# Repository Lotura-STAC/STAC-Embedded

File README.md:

# STAC-Embedded
Hardware PCB & Image

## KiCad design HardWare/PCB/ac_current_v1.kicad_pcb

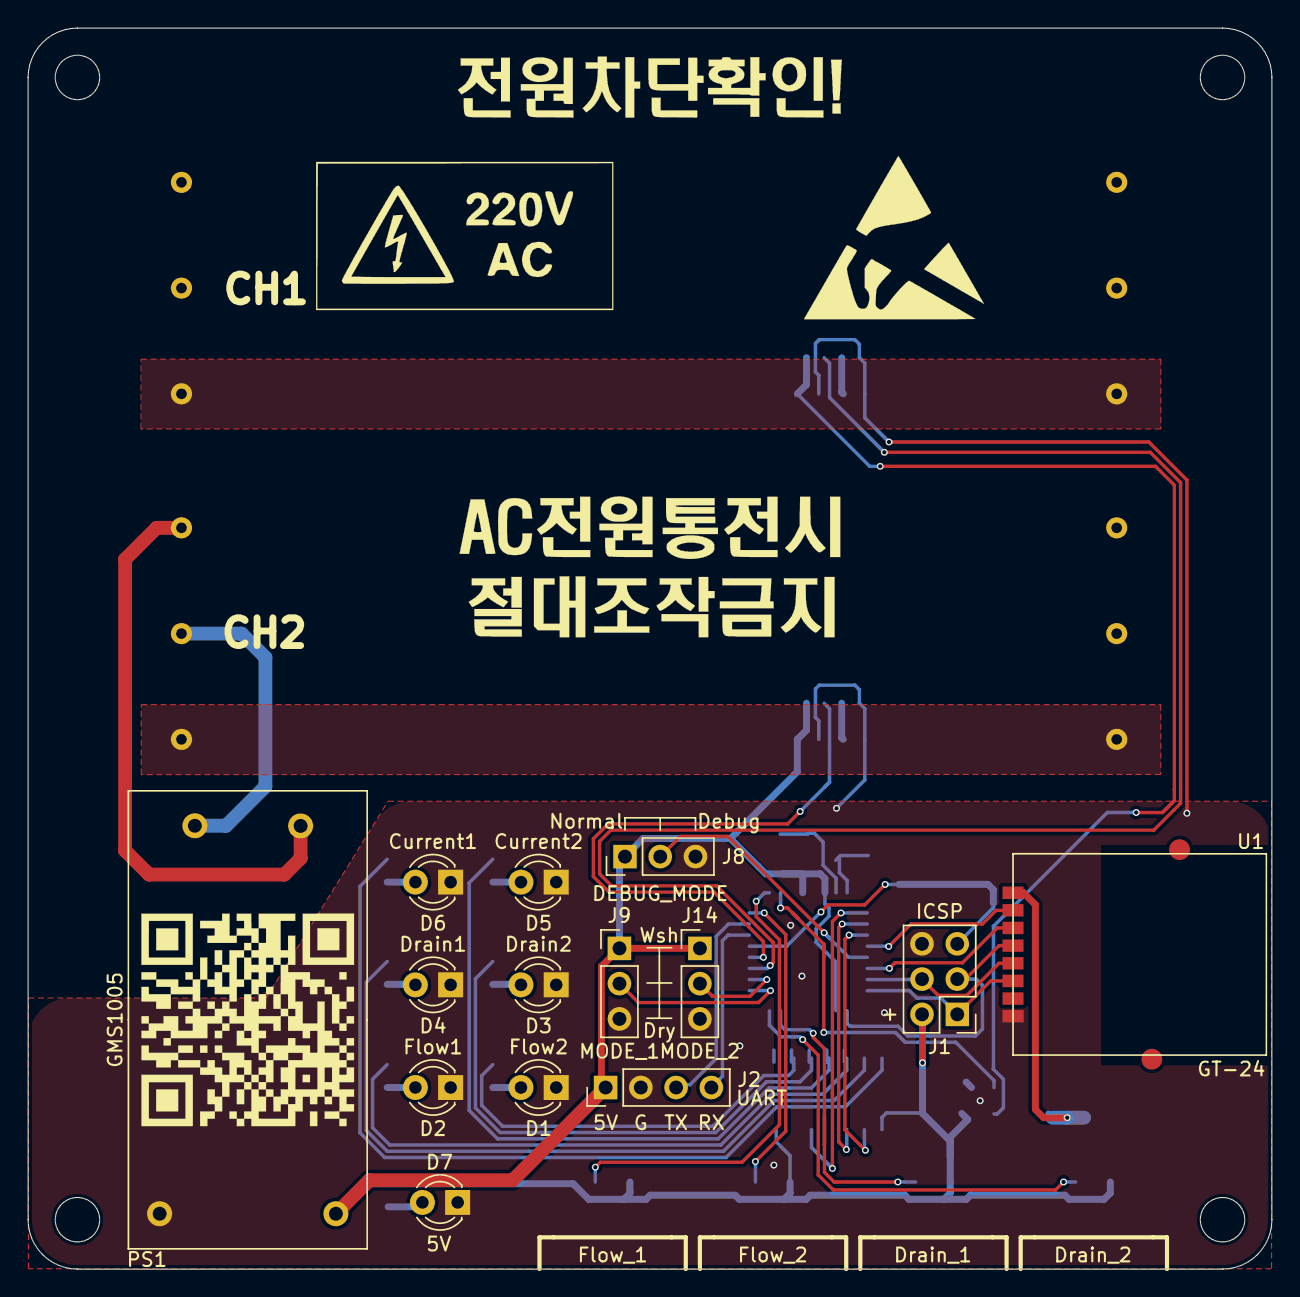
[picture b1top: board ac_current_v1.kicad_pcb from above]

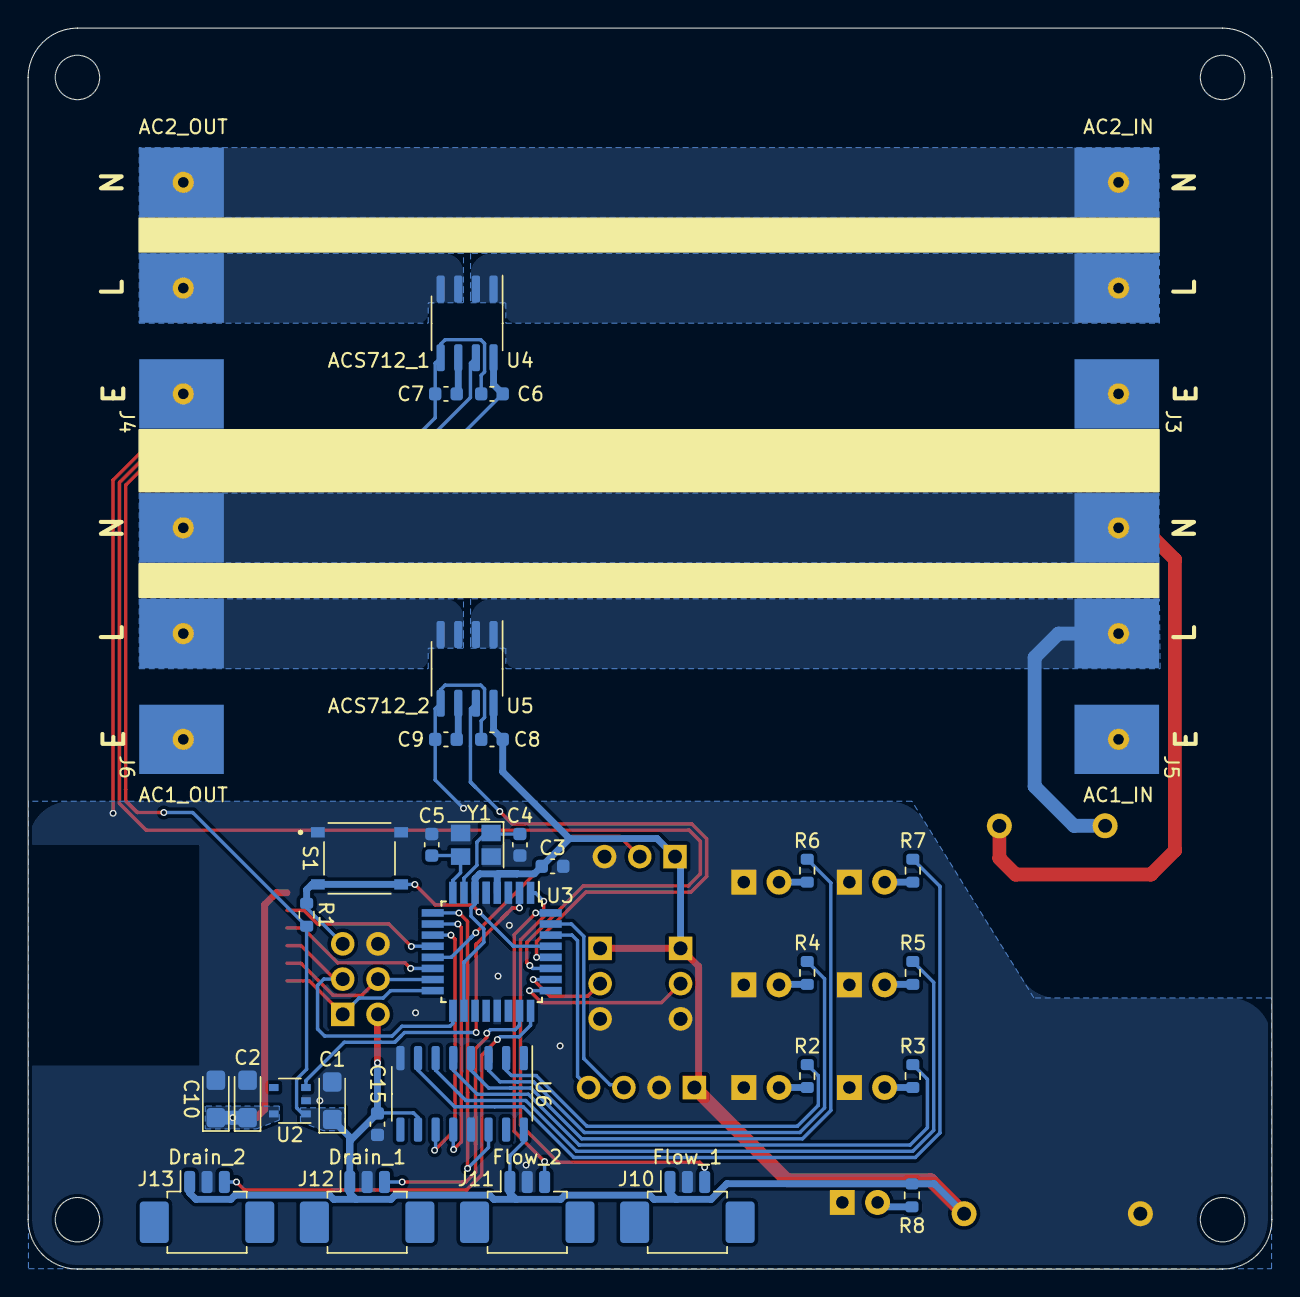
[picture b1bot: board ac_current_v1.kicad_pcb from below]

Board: 2 copper layers, 89.6 x 89.4 mm, 52 parts (34 on the bottom side), 49 nets.

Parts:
C1, C2, C10: 10uf; CP_EIA-3216-18_Kemet-A
C3, C6, C8, C15: 100nf; C_0603_1608Metric
C4, C5: 22pf; C_0603_1608Metric
C7, C9: 1nf; C_0603_1608Metric
D1: Flow2; LED_D3.0mm
D2: Flow1; LED_D3.0mm
D3: Drain2; LED_D3.0mm
D4: Drain1; LED_D3.0mm
D5: Current2; LED_D3.0mm
D6: Current1; LED_D3.0mm
D7: 5V; LED_D3.0mm
H1, H2, H3, H4: MountingHole_Pad; MountingHole_3.2mm_M3
J1: ICSP; PinHeader_2x03_P2.54mm_Vertical
J2: UART; PinHeader_1x04_P2.54mm_Vertical
J3: AC2_IN; SMD_762
J4: AC2_OUT; SMD_762
J5: AC1_IN; SMD_762
J6: AC1_OUT; SMD_762
J8: DEBUG_MODE; PinHeader_1x03_P2.54mm_Vertical
J9: MODE_1; PinHeader_1x03_P2.54mm_Vertical
J10: Flow_1; Molex_PicoBlade_53261-0371_1x03-1MP_P1.25mm_Horizontal
J11: Flow_2; Molex_PicoBlade_53261-0371_1x03-1MP_P1.25mm_Horizontal
J12: Drain_1; Molex_PicoBlade_53261-0371_1x03-1MP_P1.25mm_Horizontal
J13: Drain_2; Molex_PicoBlade_53261-0371_1x03-1MP_P1.25mm_Horizontal
J14: MODE_2; PinHeader_1x03_P2.54mm_Vertical
PS1: GMS1005; GMS0505
R1: 10k; R_0603_1608Metric
R2, R3, R4, R5, R6, R7, R8: 330; R_0603_1608Metric
S1: RST; SW_TS-1187A-B-A-B
U1: GT-24; nrf24l01 smd
U2: NCP603SN330; TSOP-5_1.65x3.05mm_P0.95mm
U3: ATmega328P-AU; TQFP-32_7x7mm_P0.8mm
U4: ACS712_1; SOIC-8_3.9x4.9mm_P1.27mm
U5: ACS712_2; SOIC-8_3.9x4.9mm_P1.27mm
U6: 74HC595; SO-16_3.9x9.9mm_P1.27mm
Y1: 16Mhz; Crystal_SMD_3225-4Pin_3.2x2.5mm

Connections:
+3V3: C2.1, C10.1, U1.1, U2.5
+5V: C1.1, C3.2, C6.1, C8.1, C15.1, J1.2, J2.1, J8.1, J9.1, J10.1, J11.1, J12.1, J13.1, J14.1, PS1.4, R1.2, R8.1, U2.1, U3.4, U3.6, U3.18, U4.8, U5.8, U6.10, U6.16
/A0: J12.3, U3.23
/A1: J13.3, U3.24
/A2: J9.2, U3.25
/A3: J14.2, U3.26
/A4: U3.27, U4.7
/A5: U3.28, U5.7
/D2: J11.3, U3.32
/D3: J10.3, U3.1
/D4: U2.3, U3.2
/D5: U3.9, U6.14
/D6: U3.10, U6.12
/D7: U3.11, U6.11
/D8: U1.2, U3.12
/D9: J8.2, U3.13
/D10: U1.3, U3.14
/D11: J1.4, U1.5, U3.15
/D12: J1.1, U1.6, U3.16
/D13: J1.3, U1.4, U3.17
/RST: J1.5, R1.1, S1.C, S1.D, U3.29
/RX: J2.4, U3.30
/TX: J2.3, U3.31
GND: C1.2, C2.2, C3.1, C4.1, C5.1, C6.2, C7.2, C8.2, C9.2, C10.2, C15.2, D1.1, D2.1, D3.1, D4.1, D5.1, D6.1, D7.1, J1.6, J2.2, J8.3, J9.3, J10.2, J11.2, J12.2, J13.2, J14.3, PS1.3, S1.A, S1.B, U1.8, U2.2, U3.3, U3.5, U3.21, U4.5, U5.5, U6.8, U6.13, Y1.2, Y1.4
GND1: J3.1, J4.1
GND2: J5.1, J6.1
LINE: J5.3, J6.3, PS1.1
NEUT: J5.2, PS1.2, U5.1, U5.2
unnamed: C4.2, U3.7, Y1.1
unnamed: C5.2, U3.8, Y1.3
unnamed: C7.1, U4.6
unnamed: C9.1, U5.6
unnamed: D1.2, R2.2
unnamed: D2.2, R3.2
unnamed: D3.2, R4.2
unnamed: D4.2, R5.2
unnamed: D5.2, R6.2
unnamed: D6.2, R7.2
unnamed: D7.2, R8.2
unnamed: J3.2, U4.1, U4.2
unnamed: J3.3, J4.3
unnamed: J4.2, U4.3, U4.4
unnamed: J6.2, U5.3, U5.4
unnamed: R2.1, U6.2
unnamed: R3.1, U6.5
unnamed: R4.1, U6.3
unnamed: R5.1, U6.6
unnamed: R6.1, U6.4
unnamed: R7.1, U6.7

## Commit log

2023-09-14 노드 펌웨어 작성, 게이트웨이 펌웨어 작성
2023-09-14 HW폴더 생성
2023-09-15 Gateway 코드 수정
2023-09-15 json 헤더 수정
2023-09-15 통신에러 수정
2023-09-18 Gateway SSL 적용
2023-09-18 HTTPS 포트 수정
2023-09-21 PCB 파일 추가, 이미지 추가
2023-09-21 주석 추가 및 함수 추가
